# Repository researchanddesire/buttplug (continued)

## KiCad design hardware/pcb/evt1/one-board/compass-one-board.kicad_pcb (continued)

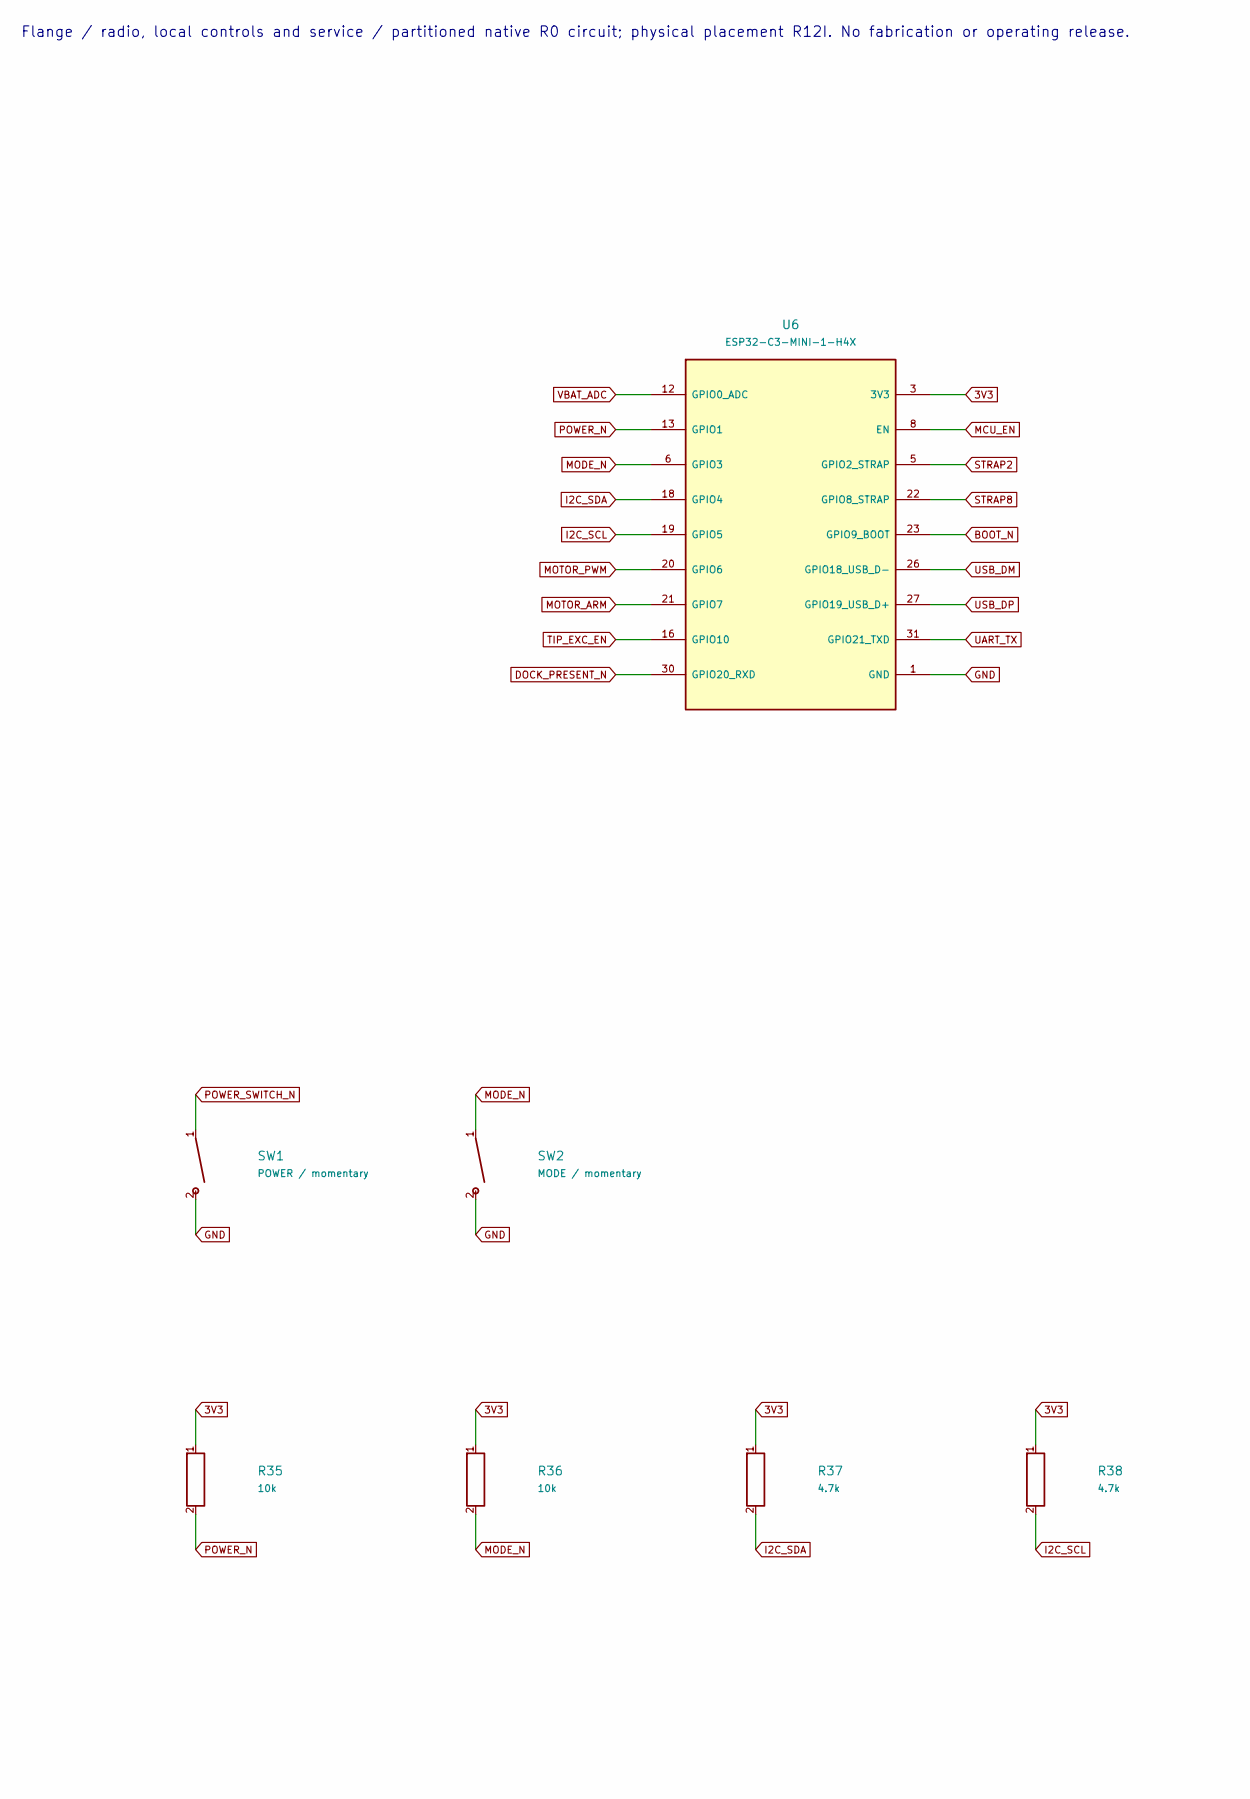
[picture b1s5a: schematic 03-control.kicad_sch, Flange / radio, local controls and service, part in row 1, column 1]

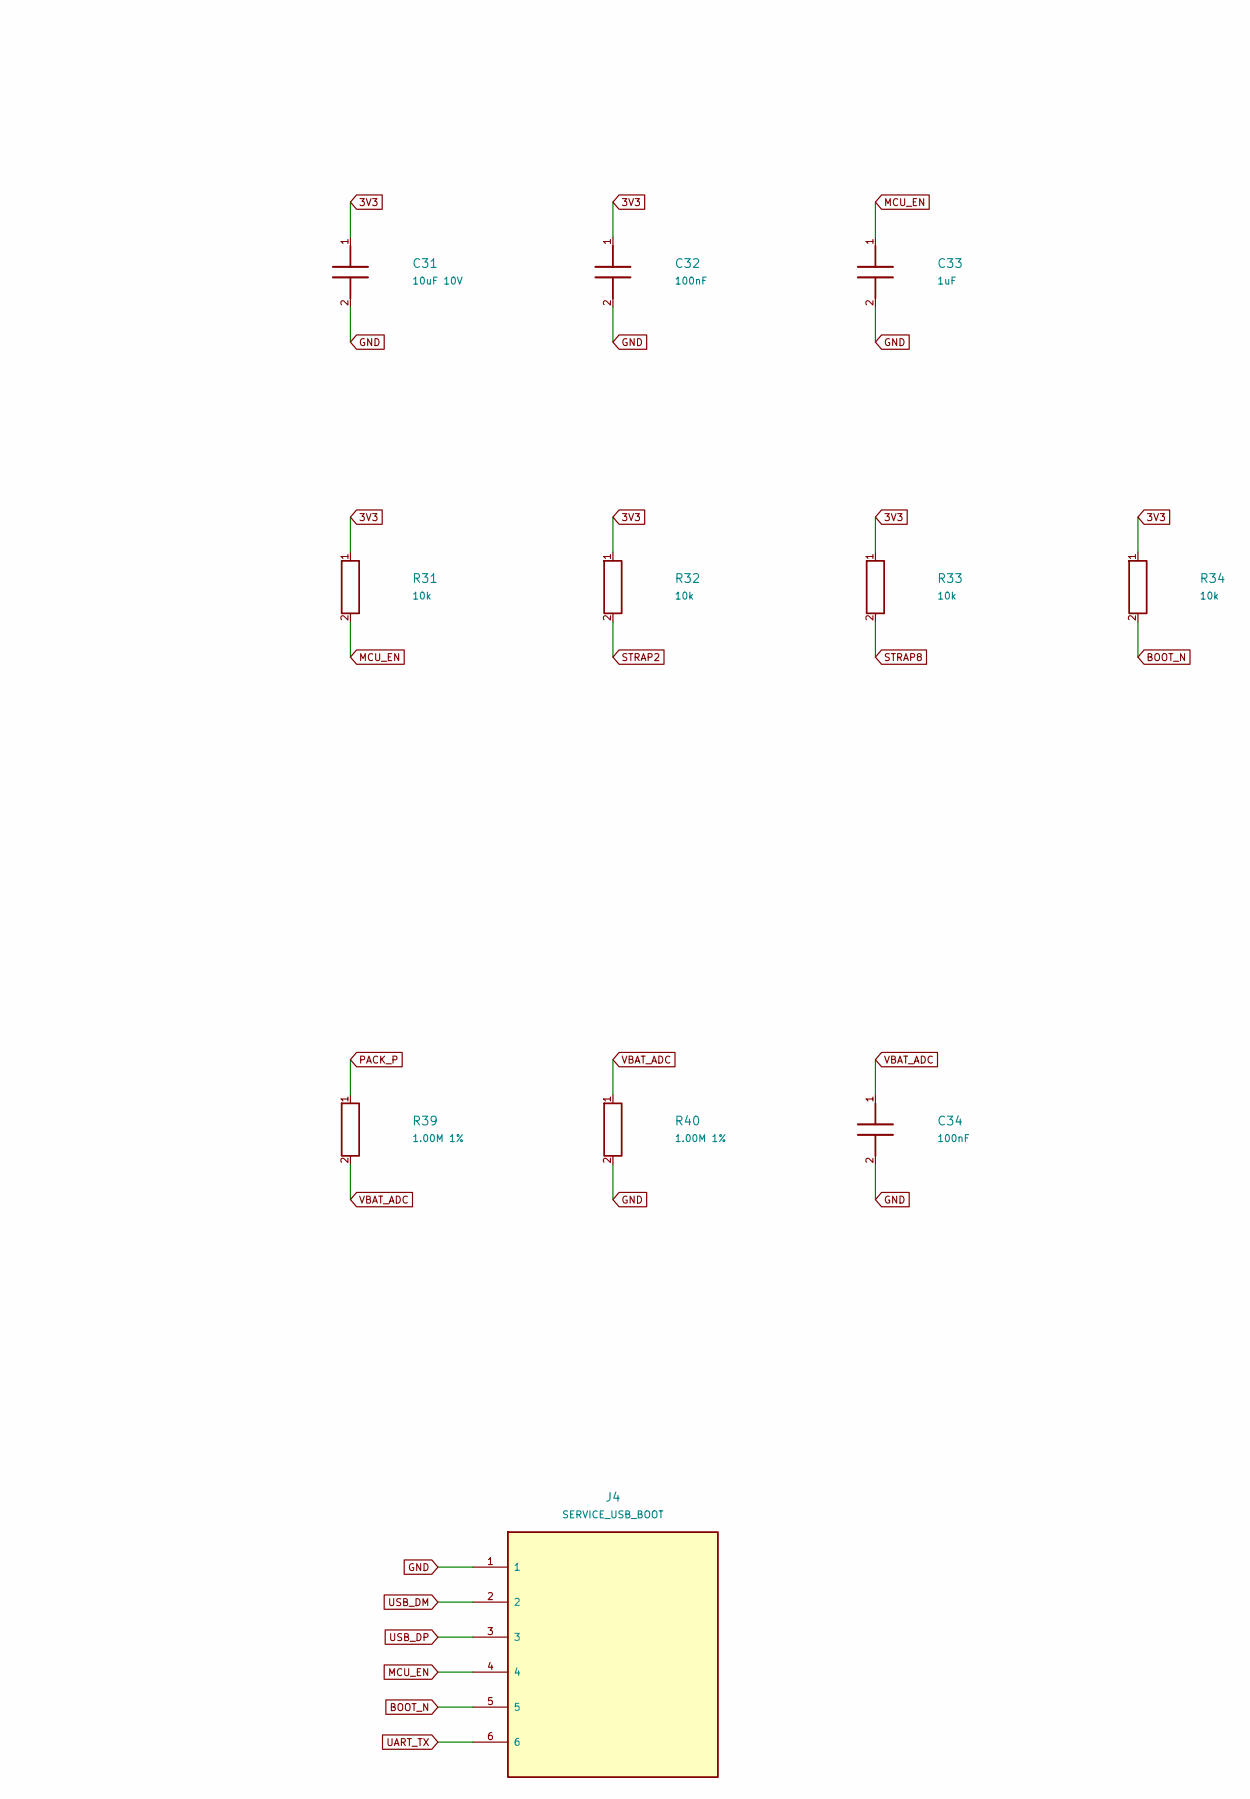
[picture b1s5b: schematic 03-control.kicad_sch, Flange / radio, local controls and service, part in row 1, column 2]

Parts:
C31: 10uF 10V; Murata_GRM21_0805_Reflow
C32, C34: 100nF; Murata_GRM18_0603_Reflow
C33: 1uF; TDK_C1608_0603_Reflow; Manufacturer Part Number CGA3E1X7R1V105KT000N; LCSC Part Number C342956
J4: SERVICE_USB_BOOT; JST_SH_SM06B-SRSS-TB_1x06-1MP_P1.00mm_Horizontal
R31, R32, R33, R34, R35, R36: 10k; Vishay_TNPW0603_IEC_Reflow
R37, R38: 4.7k; Vishay_TNPW0603_IEC_Reflow
R39, R40: 1.00M 1%; Vishay_TNPW0805_IEC_Reflow
SW1: POWER / momentary; SW_SPST_B3U-1000P
SW2: MODE / momentary; SW_SPST_B3U-1000P
U6: ESP32-C3-MINI-1-H4X; Espressif_ESP32-C3-MINI-1_53Pads; Manufacturer Part Number ESP32-C3-MINI-1-H4X; LCSC Part Number C41349510

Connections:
3V3: C31.1, C32.1, R31.1, R32.1, R33.1, R34.1, R35.1, R36.1, R37.1, R38.1, U6.3 (3V3); also elsewhere on the board
BOOT_N: J4.5, R34.2, U6.23 (GPIO9_BOOT); also elsewhere on the board
DOCK_PRESENT_N: U6.30 (GPIO20_RXD); also elsewhere on the board
GND: C31.2, C32.2, C33.2, C34.2, J4.1, R40.2, SW1.2, SW2.2, U6.1 (GND), U6.2 (GND), U6.11 (GND), U6.14 (GND), U6.36 (GND), U6.37 (GND), U6.38 (GND), U6.39 (GND), U6.40 (GND), U6.41 (GND), U6.42 (GND), U6.43 (GND), U6.44 (GND), U6.45 (GND), U6.46 (GND), U6.47 (GND), U6.48 (GND), U6.49 (GND), U6.50 (GND), U6.51 (GND), U6.52 (GND), U6.53 (GND); also elsewhere on the board
I2C_SCL: R38.2, U6.19 (GPIO5); also elsewhere on the board
I2C_SDA: R37.2, U6.18 (GPIO4); also elsewhere on the board
MCU_EN: C33.1, J4.4, R31.2, U6.8 (EN); also elsewhere on the board
MODE_N: R36.2, SW2.1, U6.6 (GPIO3); also elsewhere on the board
MOTOR_ARM: U6.21 (GPIO7); also elsewhere on the board
MOTOR_PWM: U6.20 (GPIO6); also elsewhere on the board
PACK_P: R39.1; also elsewhere on the board
POWER_N: R35.2, U6.13 (GPIO1); also elsewhere on the board
POWER_SWITCH_N: SW1.1; also elsewhere on the board
STRAP2: R32.2, U6.5 (GPIO2_STRAP)
STRAP8: R33.2, U6.22 (GPIO8_STRAP)
TIP_EXC_EN: U6.16 (GPIO10); also elsewhere on the board
UART_TX: J4.6, U6.31 (GPIO21_TXD)
USB_DM: J4.2, U6.26 (GPIO18_USB_D-); also elsewhere on the board
USB_DP: J4.3, U6.27 (GPIO19_USB_D+); also elsewhere on the board
VBAT_ADC: C34.1, R39.2, R40.1, U6.12 (GPIO0_ADC)

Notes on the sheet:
Flange / radio, local controls and service / partitioned native R0 circuit; physical placement R12I. No fabrication or operating release.

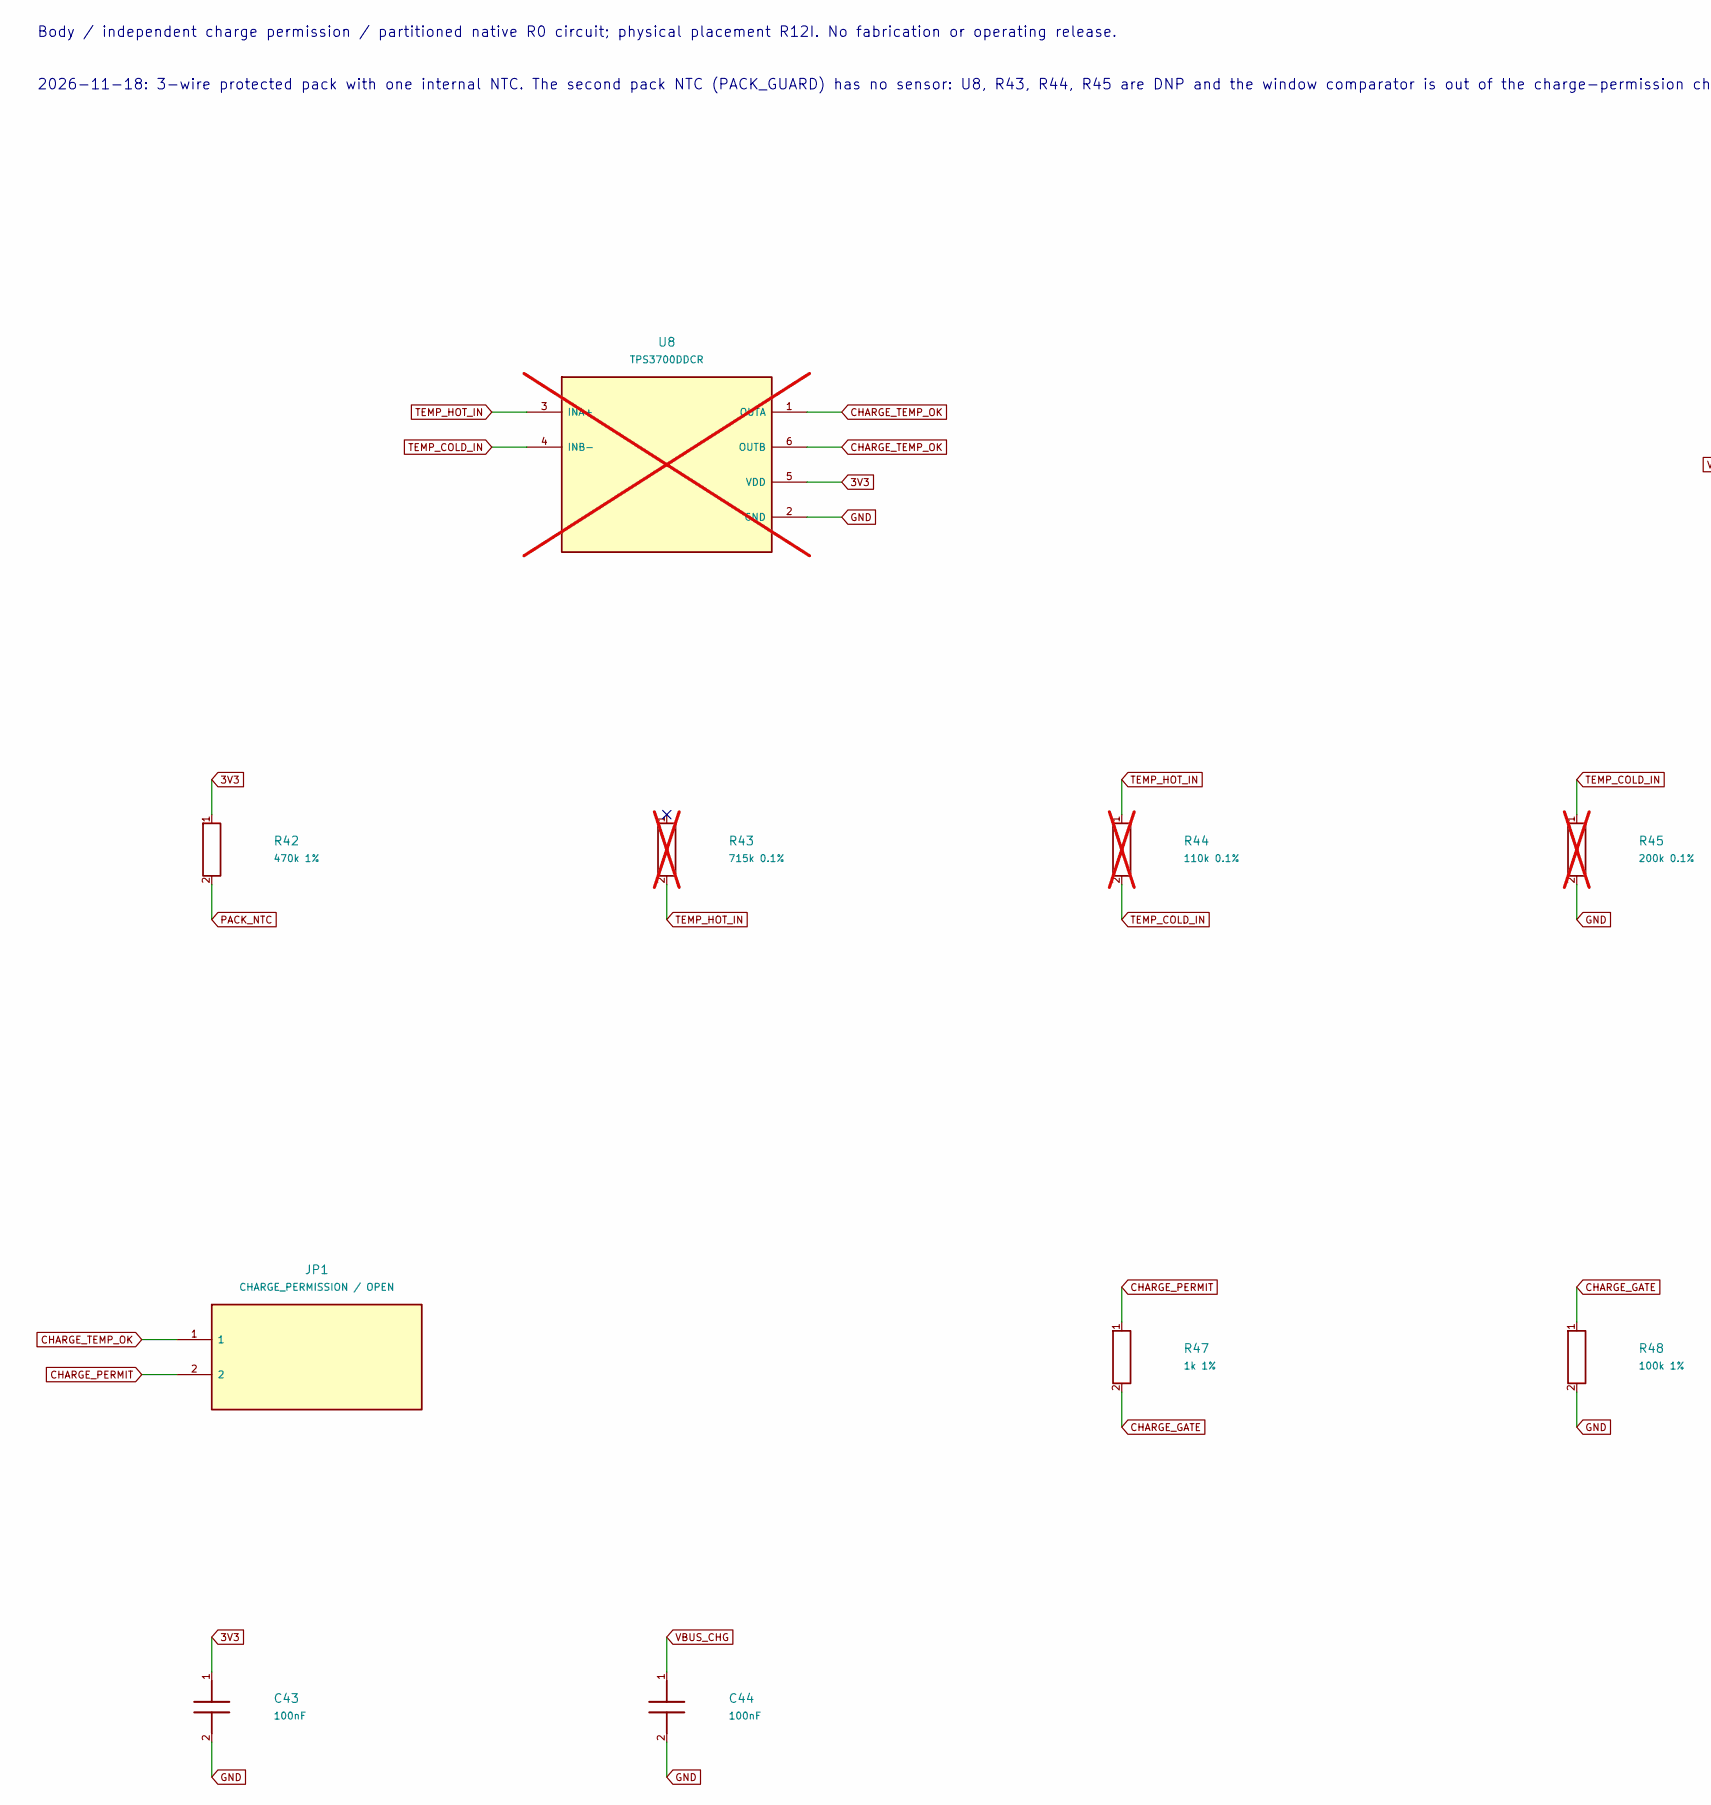
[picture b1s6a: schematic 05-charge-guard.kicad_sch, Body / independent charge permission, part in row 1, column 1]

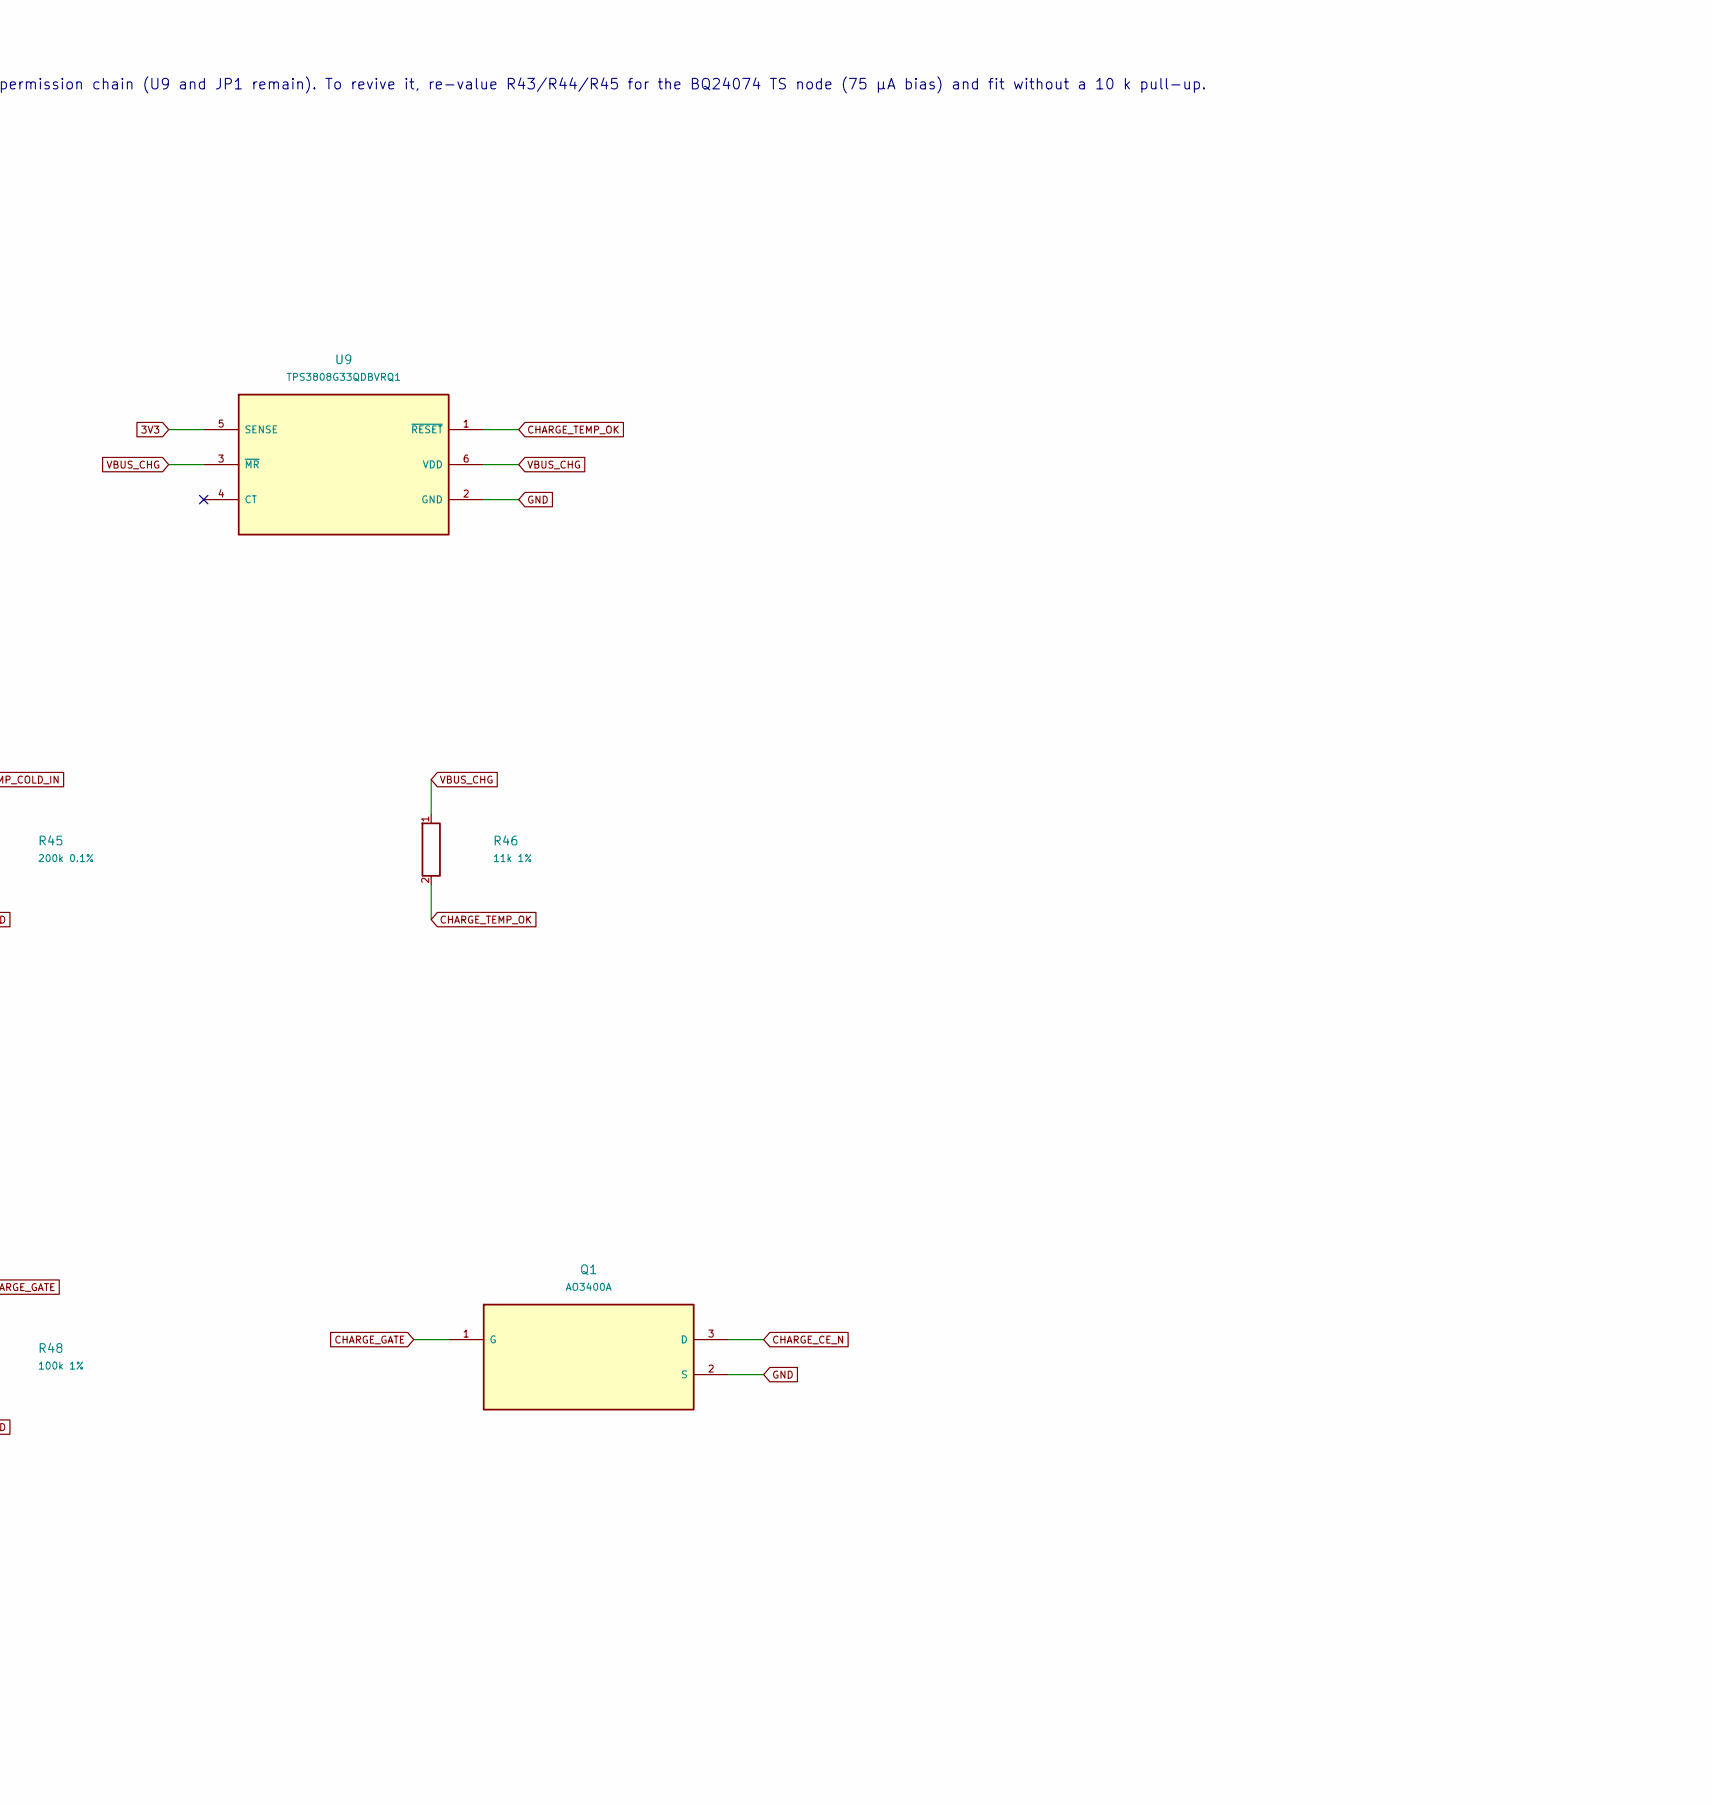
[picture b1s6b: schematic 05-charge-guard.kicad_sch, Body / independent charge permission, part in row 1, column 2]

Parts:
C43, C44: 100nF; Murata_GRM18_0603_Reflow
JP1: CHARGE_PERMISSION / OPEN; SolderJumper-2_P1.3mm_Open_RoundedPad1.0x1.5mm
Q1: AO3400A; SOT-23
R42: 470k 1%; R_0402_1005Metric; Manufacturer Part Number 0402WGF4703TCE
R43: 715k 0.1%; RESI_PTFR0805_C16003; Manufacturer Part Number PTFR0805B715KP9; LCSC Part Number C2849329; not fitted
R44: 110k 0.1%; Vishay_TNPW0603_IEC_Reflow; not fitted
R45: 200k 0.1%; Vishay_TNPW0603_IEC_Reflow; Manufacturer Part Number ERA3AEB204V; LCSC Part Number C473261; not fitted
R46: 11k 1%; R_0402_1005Metric; Manufacturer Part Number RT0402BRD0711KL; LCSC Part Number C705064
R47: 1k 1%; R_0402_1005Metric
R48: 100k 1%; R_0402_1005Metric
U8: TPS3700DDCR; TSOT-23-6; not fitted
U9: TPS3808G33QDBVRQ1; SOT-23-6; Manufacturer Part Number TPS3808G33QDBVRQ1; LCSC Part Number C414616

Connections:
3V3: C43.1, R42.1, U8.5 (VDD), U9.5 (SENSE); also elsewhere on the board
CHARGE_CE_N: Q1.3 (D); also elsewhere on the board
CHARGE_GATE: Q1.1 (G), R47.2, R48.1
CHARGE_PERMIT: JP1.2, R47.1
CHARGE_TEMP_OK: JP1.1, R46.2, U8.1 (OUTA), U8.6 (OUTB), U9.1 (~RESET)
GND: C43.2, C44.2, Q1.2 (S), R45.2, R48.2, U8.2 (GND), U9.2 (GND); also elsewhere on the board
PACK_NTC: R42.2; also elsewhere on the board
TEMP_COLD_IN: R44.2, R45.1, U8.4 (INB-)
TEMP_HOT_IN: R43.2, R44.1, U8.3 (INA+)
VBUS_CHG: C44.1, R46.1, U9.3 (~MR), U9.6 (VDD); also elsewhere on the board

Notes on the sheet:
Body / independent charge permission / partitioned native R0 circuit; physical placement R12I. No fabrication or operating release.
2026-11-18: 3-wire protected pack with one internal NTC. The second pack NTC (PACK_GUARD) has no sensor: U8, R43, R44, R45 are DNP and the window comparator is out of the charge-permission chain (U9 and JP1 remain). To revive it, re-value R43/R44/R45 for the BQ24074 TS node (75 µA bias) and fit wit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

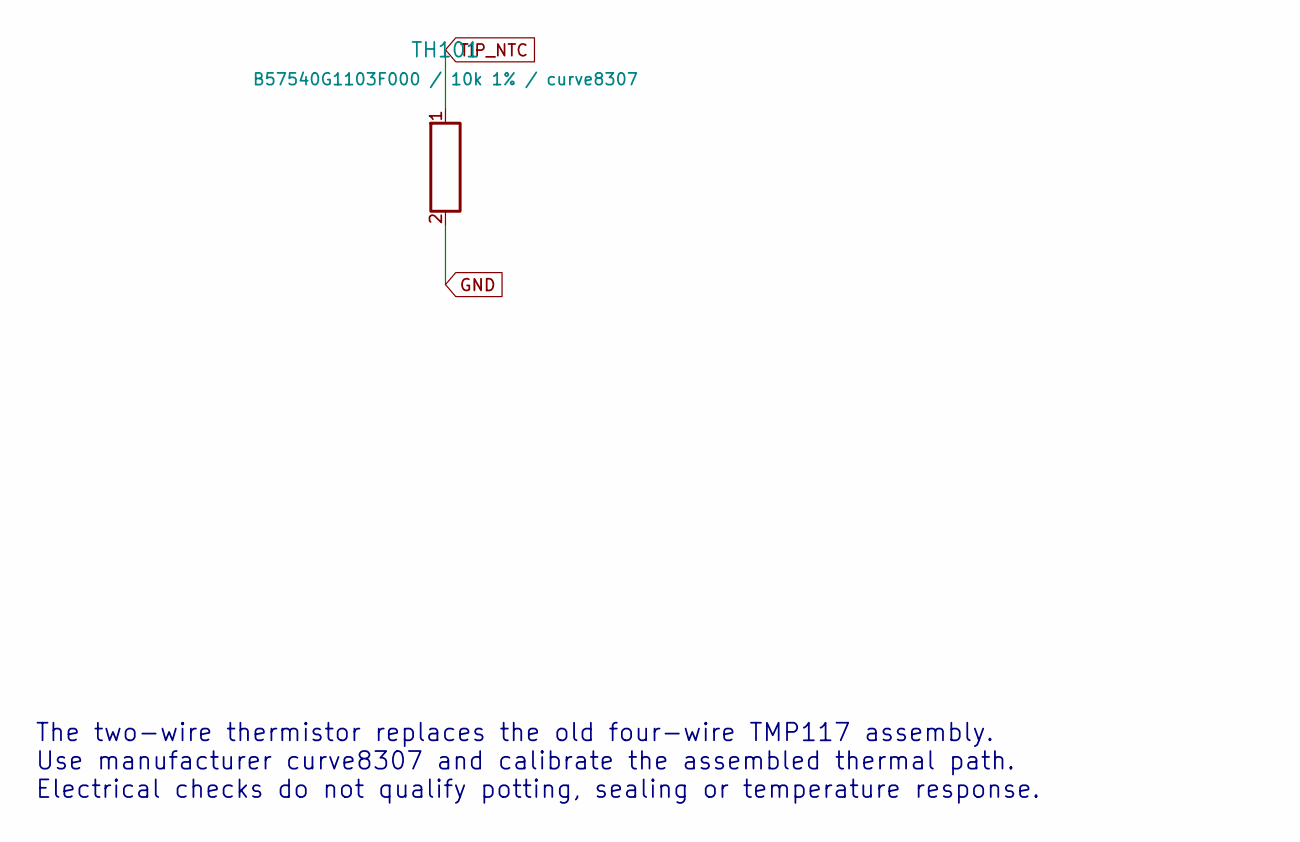
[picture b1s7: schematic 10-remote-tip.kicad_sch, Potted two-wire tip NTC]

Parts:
TH101: B57540G1103F000 / 10k 1% / curve8307

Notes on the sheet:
The two-wire thermistor replaces the old four-wire TMP117 assembly. Use manufacturer curve8307 and calibrate the assembled thermal path. Electrical checks do not qualify potting, sealing or temperature response.

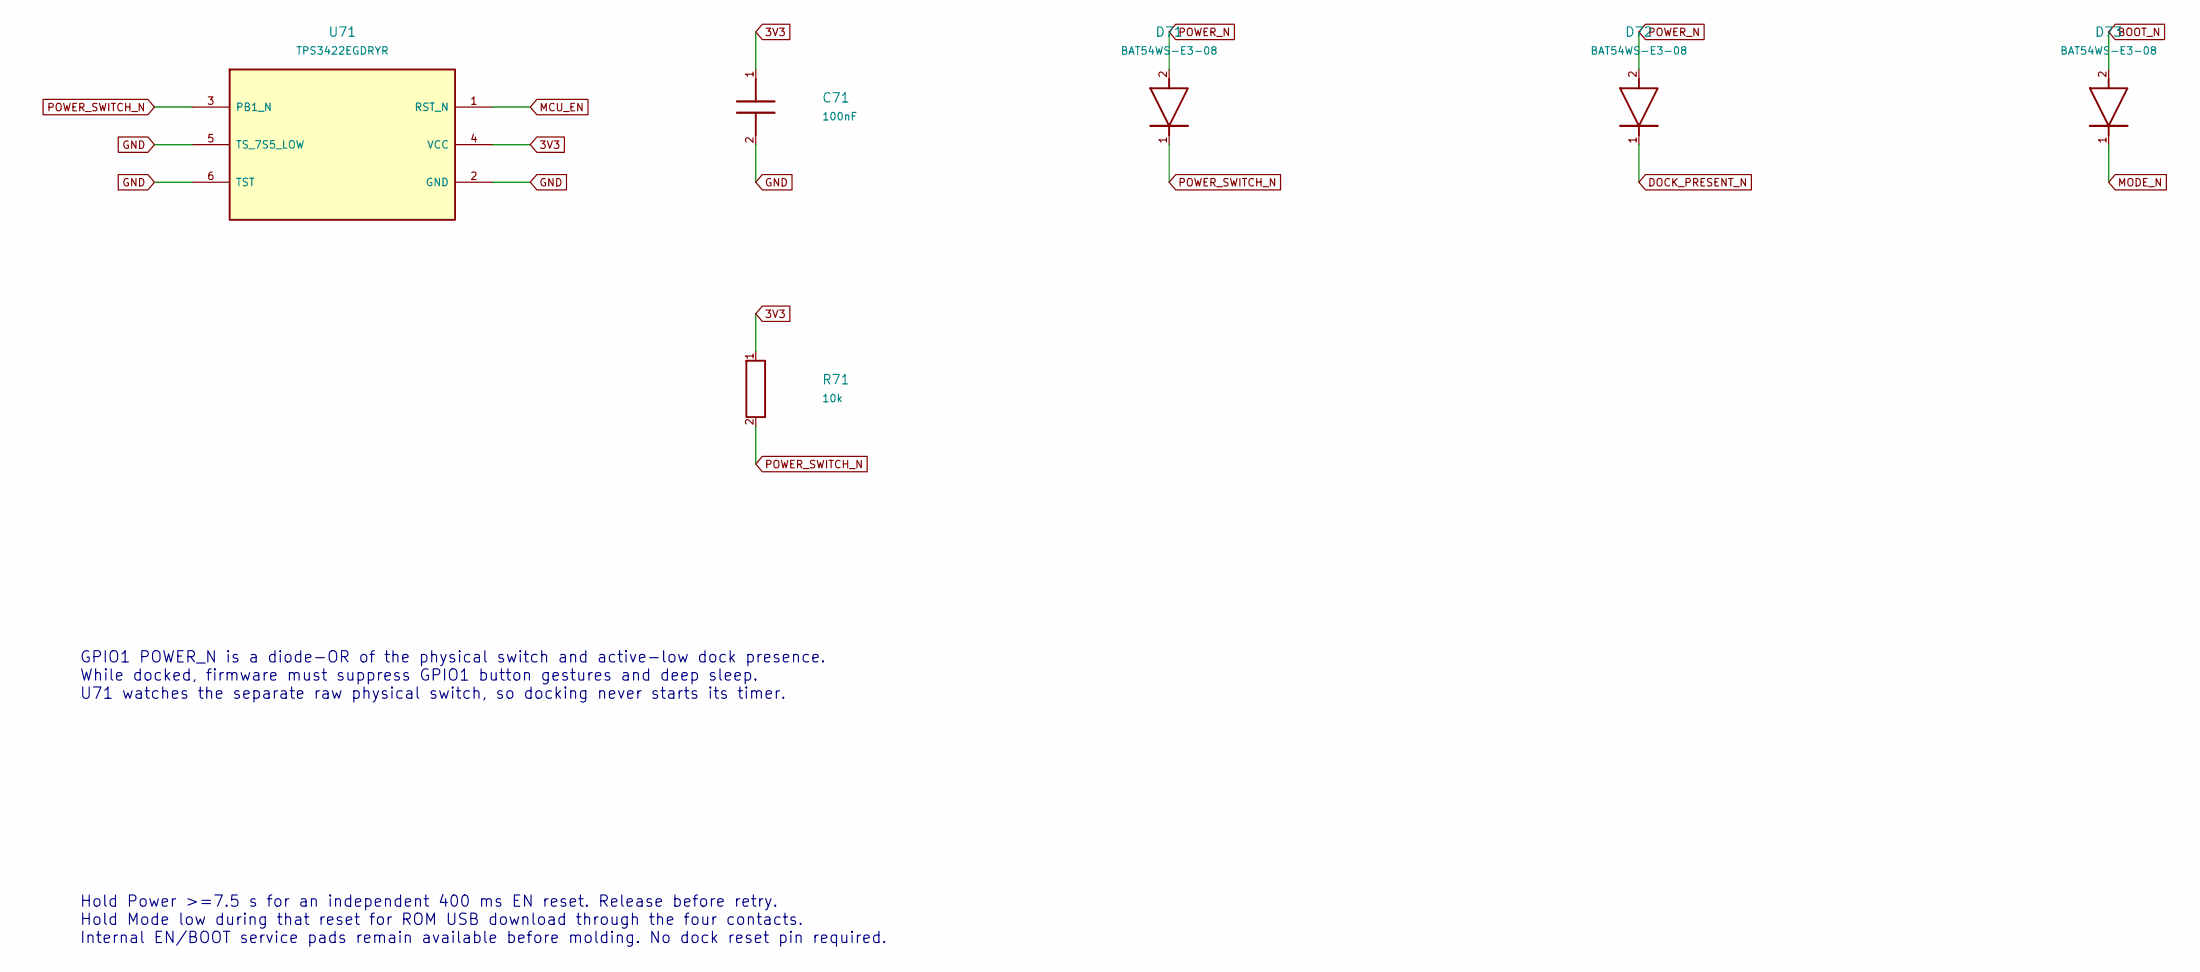
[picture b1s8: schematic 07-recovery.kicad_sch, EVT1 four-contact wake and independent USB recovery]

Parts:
C71: 100nF; C_0402_1005Metric
D71, D72, D73: BAT54WS-E3-08; D_SOD-323
R71: 10k; R_0402_1005Metric
U71: TPS3422EGDRYR; Texas_USON-6_1x1.45mm_P0.5mm_SMD

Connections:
3V3: C71.1, R71.1, U71.4 (VCC); also elsewhere on the board
BOOT_N: D73.2 (1); also elsewhere on the board
DOCK_PRESENT_N: D72.1 (2); also elsewhere on the board
GND: C71.2, U71.2 (GND), U71.5 (TS_7S5_LOW), U71.6 (TST); also elsewhere on the board
MCU_EN: U71.1 (RST_N); also elsewhere on the board
MODE_N: D73.1 (2); also elsewhere on the board
POWER_N: D71.2 (1), D72.2 (1); also elsewhere on the board
POWER_SWITCH_N: D71.1 (2), R71.2, U71.3 (PB1_N); also elsewhere on the board

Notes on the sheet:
Hold Power >=7.5 s for an independent 400 ms EN reset. Release before retry. Hold Mode low during that reset for ROM USB download through the four contacts. Internal EN/BOOT service pads remain available before molding. No dock reset pin required.
GPIO1 POWER_N is a diode-OR of the physical switch and active-low dock presence. While docked, firmware must suppress GPIO1 button gestures and deep sleep. U71 watches the separate raw physical switch, so docking never starts its timer.

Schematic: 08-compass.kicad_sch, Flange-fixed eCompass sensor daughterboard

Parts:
C81: 220nF; C_0402_1005Metric
C82: 100nF; C_0402_1005Metric
C83: 47uF 10V / Ceff>=10uF at3V3; C_0805_2012Metric; Manufacturer Part Number MSASL21GBB5476MTNA01; LCSC Part Number C386058
C84: 100nF / VDDIO local; C_0402_1005Metric
U81: LSM303AGRTR; LGA-12_2x2mm_P0.5mm

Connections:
3V3: C82.1, C83.1, C84.1, U81.2 (CS_XL), U81.3 (CS_MAG), U81.9 (VDD), U81.10 (VDDIO); also elsewhere on the board
GND: C81.2, C82.2, C83.2, C84.2, U81.6 (GND), U81.8 (GND); also elsewhere on the board
I2C_SCL: U81.1 (SCL); also elsewhere on the board
I2C_SDA: U81.4 (SDA); also elsewhere on the board
MAG_C1: C81.1, U81.5 (C1)

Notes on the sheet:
Both sensor axes are fixed to the flange/back-arrow reference, independent of cap rotation. Place near +X flange end, away from motor, steel keepers and charging magnets. No extra pullups: existing R32/R33 pull up the common 3V3 I2C bus. Register axes to CAD. Calibrate assembled magnetic offsets; s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

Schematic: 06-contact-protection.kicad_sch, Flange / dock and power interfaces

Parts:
D1: Schottky 1A/20V candidate; Diodes_B140HW_SOD123_A1_K2
F1: PTC 500mA candidate; Fuse_1206_3216Metric
R75, R76: 22R; R_0402_1005Metric; Manufacturer Part Number RC0402FR-0722RL; LCSC Part Number C114765
U75: USBLC6-2SC6; SOT-23-6

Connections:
DOCK_5V: F1.1, U75.5 (VBUS); also elsewhere on the board
DOCK_FUSED: D1.1, F1.2
GND: U75.2 (GND); also elsewhere on the board
USB_DM: R75.2; also elsewhere on the board
USB_DM_CONTACT: R75.1, U75.1 (IO1_IN), U75.6 (IO1_OUT); also elsewhere on the board
USB_DP: R76.2; also elsewhere on the board
USB_DP_CONTACT: R76.1, U75.3 (IO2_IN), U75.4 (IO2_OUT); also elsewhere on the board
VBUS_CHG: D1.2; also elsewhere on the board

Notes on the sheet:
Flange / dock and power interfaces / partitioned native R0 circuit; physical placement R12I. No fabrication or operating release.
Native USB: D- to GPIO18, D+ to GPIO19. Place R75/R76 near MCU. Contact order from -X: GND / D- / D+ / 5V. Place U75 at contact entry. Internal J4 is before series resistors; do not connect two USB hosts simultaneously.

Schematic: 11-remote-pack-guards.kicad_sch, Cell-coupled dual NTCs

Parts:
TH1: Pack internal NTC 10k (B 3435 typ.)

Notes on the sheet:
Pack internal NTC (3-wire protected pack) / no separate cell-mounted sensors since 2026-11-18. No fabrication or operating release.
